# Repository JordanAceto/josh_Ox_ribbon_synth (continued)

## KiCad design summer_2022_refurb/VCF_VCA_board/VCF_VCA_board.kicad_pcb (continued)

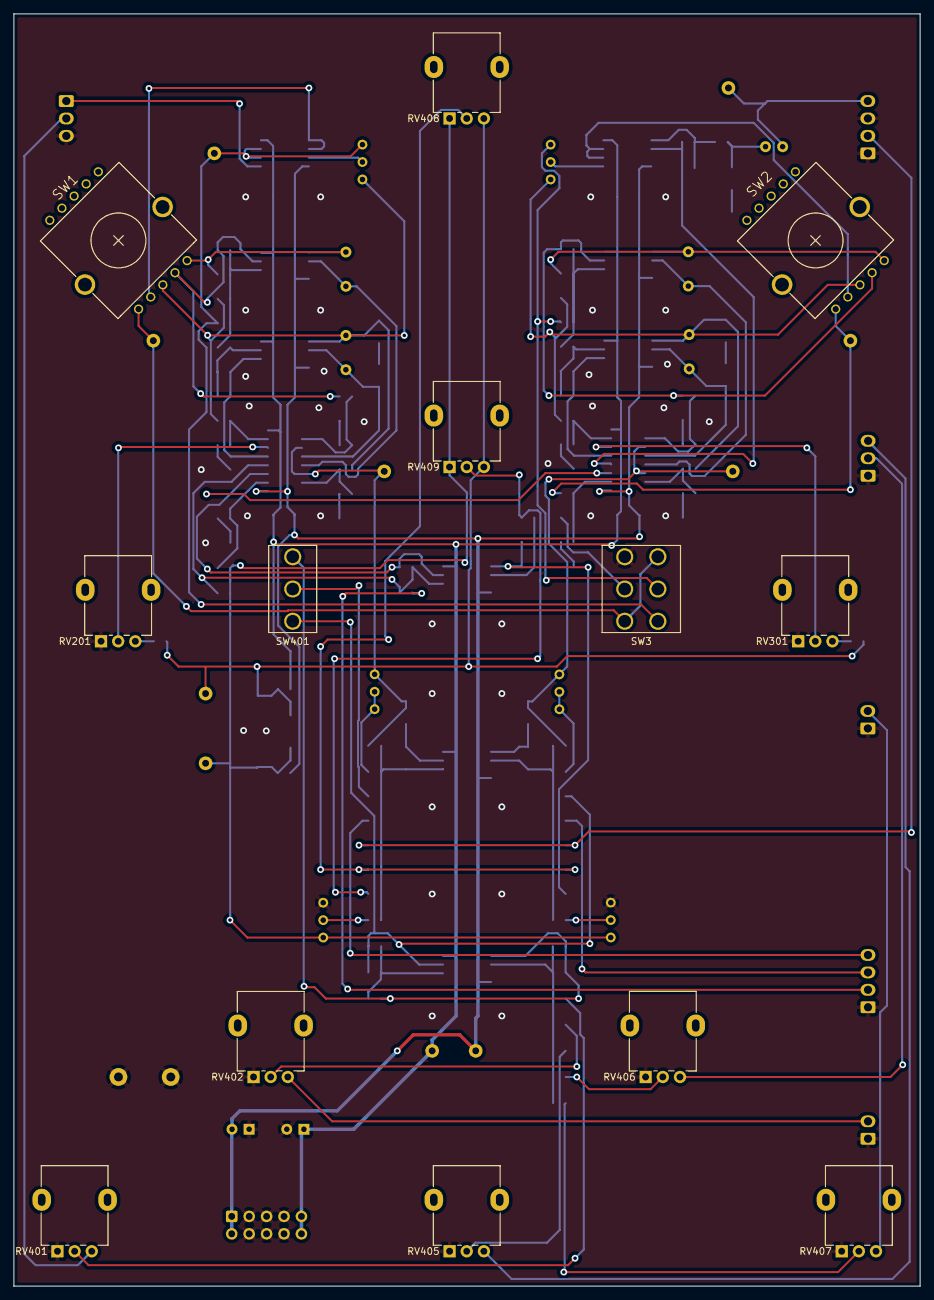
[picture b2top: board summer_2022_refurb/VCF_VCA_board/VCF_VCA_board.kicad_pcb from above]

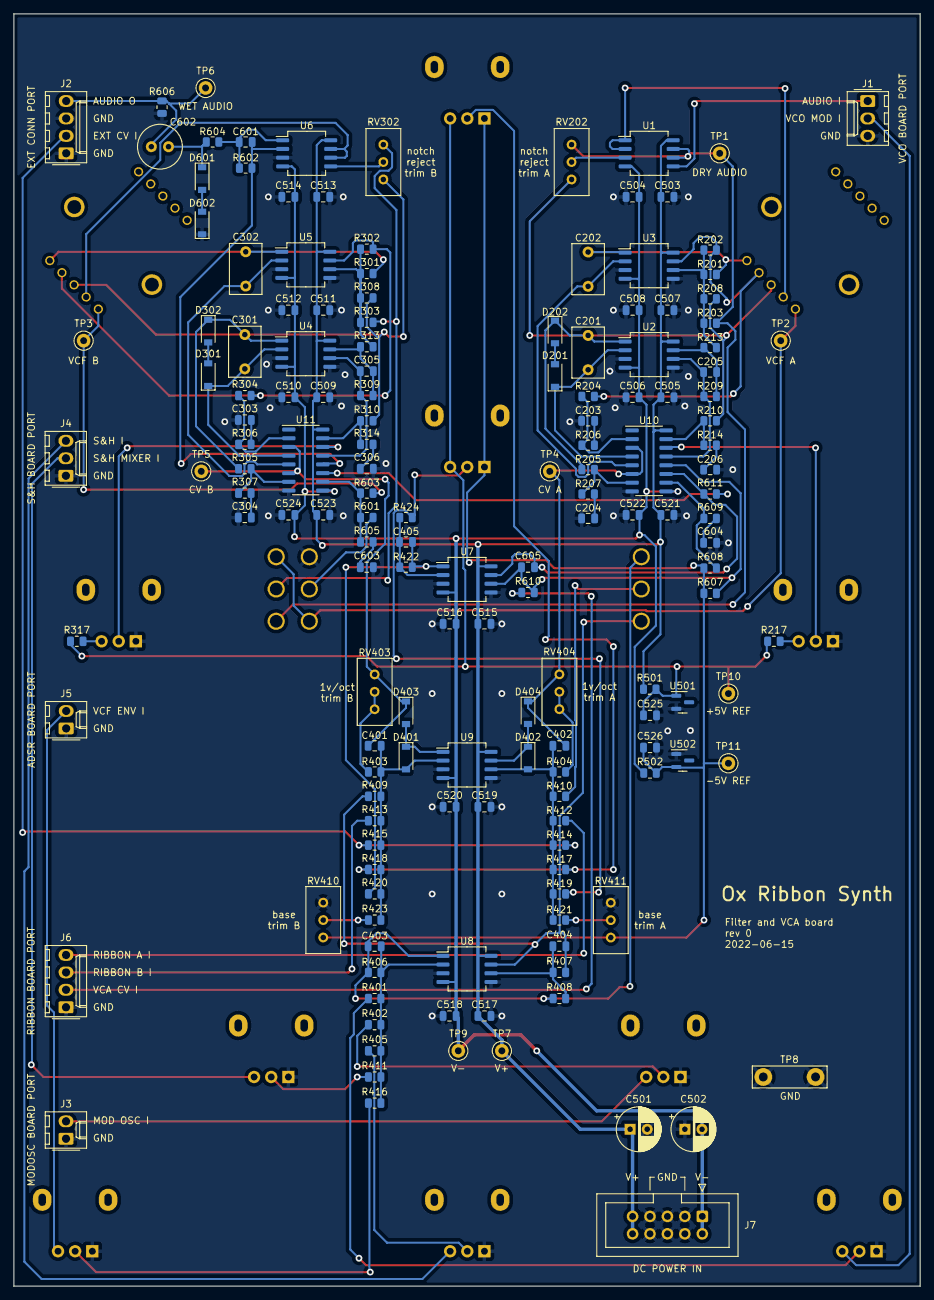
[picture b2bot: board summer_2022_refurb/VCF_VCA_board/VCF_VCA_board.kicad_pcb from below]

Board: 2 copper layers, 132.1 x 185.4 mm, 171 parts (158 on the bottom side), 94 nets.

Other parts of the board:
C301, C302: 220p; C_Rect_L7.2mm_W4.5mm_P5.00mm_FKS2_FKP2_MKS2_MKP2
C303, C304, C306: 560p; C_0805_2012Metric
C305: C; C_0805_2012Metric
D301, D302: 3v9; D_SOD-123
R301, R302, R303, R304, R305, R309, R313: 30k; R_0805_2012Metric
R306, R307, R314: 510; R_0805_2012Metric
R308: 270k; R_0805_2012Metric
R310: 15k; R_0805_2012Metric
R317: R; R_0805_2012Metric
RV301: 100k; Potentiometer_Alpha_RD901F-40-00D_Single_Vertical
RV302: 50k; Potentiometer_Bourns_3296W_Vertical

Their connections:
+5V REF: R317.1; also elsewhere on the board
/SVF_B/BP_OUT: C301.2, D302.1 (K), R305.1, R308.2, R310.2, RV302.3; also elsewhere on the board
/SVF_B/HP_OUT: R302.2, R304.1; also elsewhere on the board
/SVF_B/LP_OUT: C302.2, R301.2; also elsewhere on the board
/SVF_B/SIGNAL_IN: R303.1, RV302.1; also elsewhere on the board
unnamed 35: C301.1, D301.1 (K); also elsewhere on the board
unnamed 36: C302.1; also elsewhere on the board
unnamed: C303.1, R306.2
unnamed: C304.1, R307.2
unnamed 39: C305.1, R309.2, R313.2; also elsewhere on the board
unnamed 40: C305.2, R309.1; also elsewhere on the board
unnamed: C306.1, R314.2
unnamed: D301.2 (A), D302.2 (A)
unnamed 68: R301.1, R302.1, R303.2, R308.1, R313.1; also elsewhere on the board
unnamed 69: R304.2, R306.1; also elsewhere on the board
unnamed 70: R305.2, R307.1; also elsewhere on the board
unnamed 71: R310.1, R314.1; also elsewhere on the board
unnamed: R317.2, RV301.3
unnamed 90: RV301.2; also elsewhere on the board
unnamed 91: RV302.2; also elsewhere on the board

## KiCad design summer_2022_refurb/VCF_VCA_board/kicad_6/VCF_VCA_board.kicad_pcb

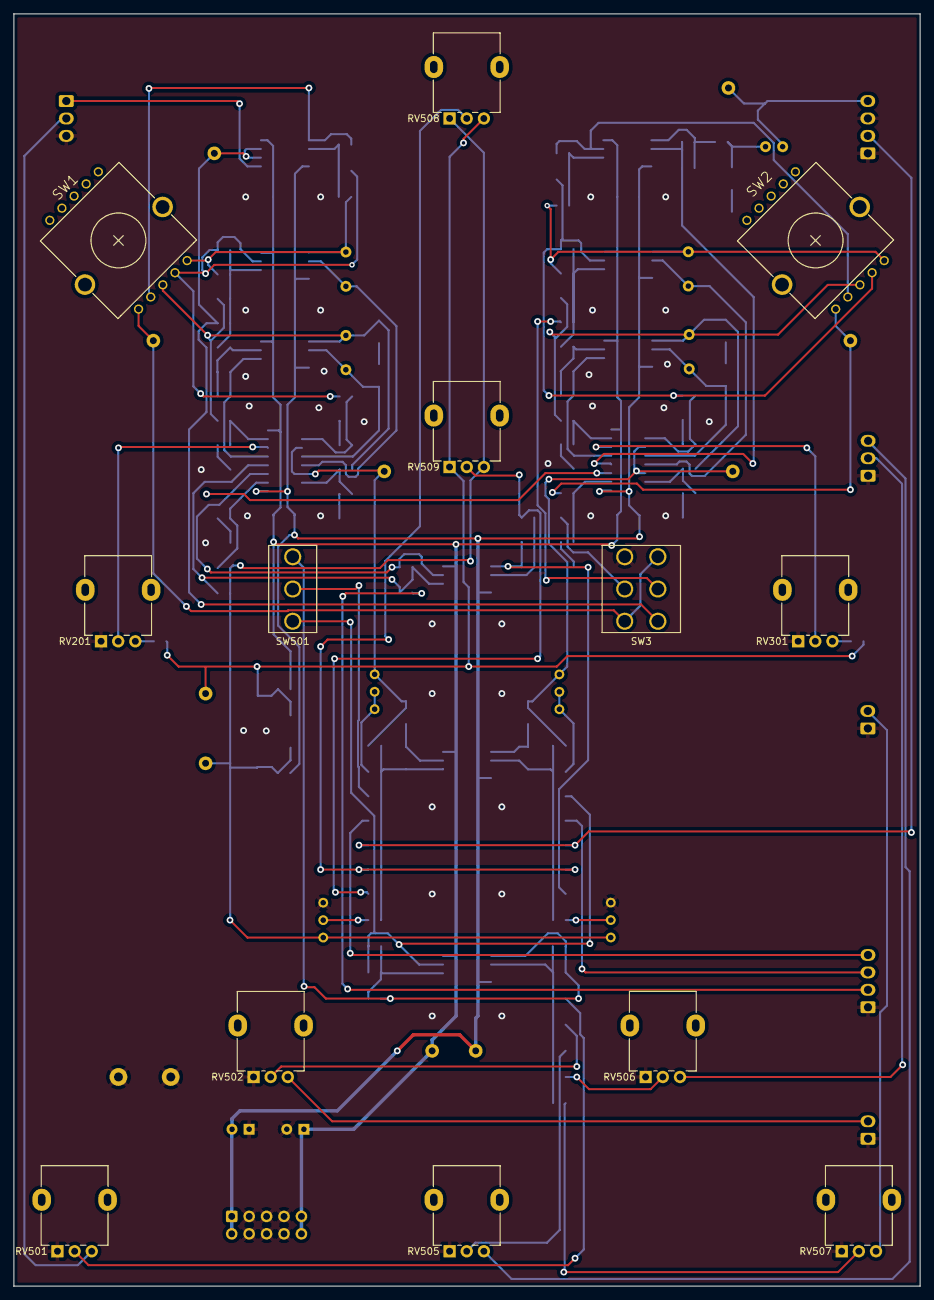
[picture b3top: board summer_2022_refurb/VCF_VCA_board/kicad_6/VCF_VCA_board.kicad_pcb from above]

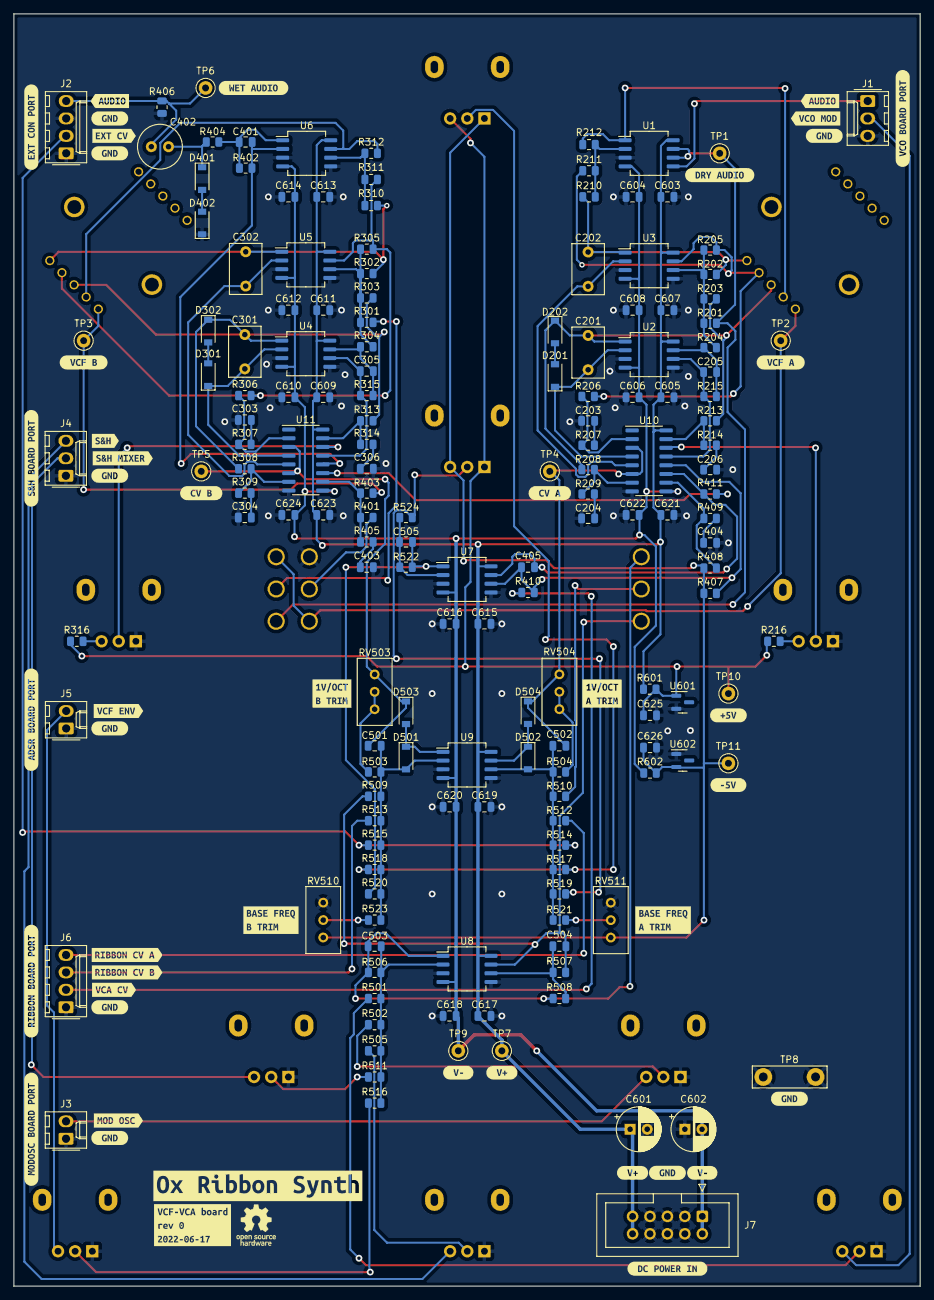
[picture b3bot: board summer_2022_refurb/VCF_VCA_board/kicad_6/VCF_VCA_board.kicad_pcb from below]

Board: 2 copper layers, 132.1 x 185.4 mm, 220 parts (207 on the bottom side), 94 nets.

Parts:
C201, C202, C301, C302: 220p; C_Rect_L7.2mm_W4.5mm_P5.00mm_FKS2_FKP2_MKS2_MKP2
C203, C204, C206, C303, C304, C306, C403, C404: 1n2; C_0805_2012Metric
C205, C305: C; C_0805_2012Metric
C401, C405, C501, C502, C503, C504, C505: 100p; C_0805_2012Metric
C402: 10u; C_Radial_D6.3mm_H5.0mm_P2.50mm
C601, C602: 10u; CP_Radial_D6.3mm_P2.50mm
C603, C604, C605, C606, C607, C608, C609, C610, C611, C612, C613, C614, C615, C616, C617, C618, C619, C620, C621, C622, C623, C624, C625, C626: 100n; C_0805_2012Metric
D201, D202, D301, D302: 3v9; D_SOD-123
D401, D402: D_Zener; D_SOD-123
D501, D502, D503, D504: 1N4148W; D_SOD-123
J1: VCO_port; Molex_KK-254_AE-6410-03A_1x03_P2.54mm_Vertical
J2: ext_port; Molex_KK-254_AE-6410-04A_1x04_P2.54mm_Vertical
J3: mod_osc_port; Molex_KK-254_AE-6410-02A_1x02_P2.54mm_Vertical
J4: S&H_port; Molex_KK-254_AE-6410-03A_1x03_P2.54mm_Vertical
J5: ADSR_port; Molex_KK-254_AE-6410-02A_1x02_P2.54mm_Vertical
J6: ribbon_port; Molex_KK-254_AE-6410-04A_1x04_P2.54mm_Vertical
J7: power_entry; IDC-Header_2x05_P2.54mm_Vertical
R201, R202, R204, R205, R206, R208, R210, R211, R212, R215, R301, R302, R304, R305, R306, R308, R310, R311, R312, R315, R401, R402, R403: 30k; R_0805_2012Metric
R203, R303: 270k; R_0805_2012Metric
R207, R209, R214, R307, R309, R314, R405, R409: 220; R_0805_2012Metric
R213, R313, R503, R504: 15k; R_0805_2012Metric
R216, R316: R; R_0805_2012Metric
R404: 1k; R_0805_2012Metric
R406, R408, R410, R501, R502, R505, R506, R507, R508, R509, R510, R511, R512, R513, R514, R515, R516, R517, R518, R522, R524: 100k; R_0805_2012Metric
R407: 2M2; R_0805_2012Metric
R411: 4k7; R_0805_2012Metric
R519, R520, R521, R523: ?; R_0805_2012Metric
R601, R602: 5k6; R_0805_2012Metric
RV201, RV301, RV501, RV502, RV505, RV506, RV507, RV508, RV509: 100k; Potentiometer_Alpha_RD901F-40-00D_Single_Vertical
RV503, RV504, RV510, RV511: 5k; Potentiometer_Bourns_3296W_Vertical
SW1, SW2: SR1712F-0204; SR1712F_rotary_switch
SW3: series_parallel_switch; DPDT_mini_toggle
SW501: SW_SPDT_center_off; SPDT_mini_toggle
TP1: DRY; TestPoint_Keystone_5000-5004_Miniature
TP2: VCF_A; TestPoint_Keystone_5000-5004_Miniature
TP3: VCF_B; TestPoint_Keystone_5000-5004_Miniature
TP4: CV_A; TestPoint_Keystone_5000-5004_Miniature
TP5: CV_B; TestPoint_Keystone_5000-5004_Miniature
TP6: FINAL_AUDIO; TestPoint_Keystone_5000-5004_Miniature
TP7: V+; TestPoint_Keystone_5000-5004_Miniature
TP8: GND; TestPoint_Bridge_Pitch7.62mm_Drill1.3mm
TP9: V-; TestPoint_Keystone_5000-5004_Miniature
TP10: REF+; TestPoint_Keystone_5000-5004_Miniature
TP11: REF-; TestPoint_Keystone_5000-5004_Miniature
U1, U2, U3, U4, U5, U6, U7, U8, U9: TL072; SO-8_5.3x6.2mm_P1.27mm
U10, U11: SSI2164; SOIC-16_3.9x9.9mm_P1.27mm
U601, U602: LM4040DBZ-5; SOT-23
kibuzzard-62AC7A9F: G***; kibuzzard-62AC7A9F
kibuzzard-62AC8A1C: G***; kibuzzard-62AC8A1C
kibuzzard-62AC8A2D: G***; kibuzzard-62AC8A2D
kibuzzard-62AC8A4C: G***; kibuzzard-62AC8A4C
kibuzzard-62AC8A9A: G***; kibuzzard-62AC8A9A
kibuzzard-62AC8A40: G***; kibuzzard-62AC8A40
kibuzzard-62AC8A61: G***; kibuzzard-62AC8A61
kibuzzard-62AC8A72: G***; kibuzzard-62AC8A72
kibuzzard-62AC8A87: G***; kibuzzard-62AC8A87
kibuzzard-62AC8B01: G***; kibuzzard-62AC8B01
kibuzzard-62AC8B2D: G***; kibuzzard-62AC8B2D
kibuzzard-62AC8B15: G***; kibuzzard-62AC8B15
kibuzzard-62AC8B47: G***; kibuzzard-62AC8B47
kibuzzard-62AC78CB: G***; kibuzzard-62AC78CB
kibuzzard-62AC88AD: G***; kibuzzard-62AC88AD
kibuzzard-62AC88C6: G***; kibuzzard-62AC88C6
kibuzzard-62AC88DA: G***; kibuzzard-62AC88DA
kibuzzard-62AC88EB: G***; kibuzzard-62AC88EB
kibuzzard-62AC89A8: G***; kibuzzard-62AC89A8
kibuzzard-62AC89C0: G***; kibuzzard-62AC89C0
kibuzzard-62AC89D1: G***; kibuzzard-62AC89D1
kibuzzard-62AC89EA: G***; kibuzzard-62AC89EA
kibuzzard-62AC755C, kibuzzard-62AC755C#2, kibuzzard-62AC755C#3, kibuzzard-62AC755C#4, kibuzzard-62AC755C#5, kibuzzard-62AC755C#6, kibuzzard-62AC755C#7, kibuzzard-62AC755C#8, kibuzzard-62AC755C#9: G***; kibuzzard-62AC755C
kibuzzard-62AC791A, kibuzzard-62AC791A#2: G***; kibuzzard-62AC791A
kibuzzard-62AC792A, kibuzzard-62AC792A#2: G***; kibuzzard-62AC792A
kibuzzard-62AC886F: G***; kibuzzard-62AC886F
kibuzzard-62AC887D: G***; kibuzzard-62AC887D
kibuzzard-62AC892A, kibuzzard-62AC892A#2: G***; kibuzzard-62AC892A
kibuzzard-62AC8760: G***; kibuzzard-62AC8760
kibuzzard-62AC8892: G***; kibuzzard-62AC8892
kibuzzard-62AC8908: G***; kibuzzard-62AC8908
kibuzzard-62AC8951: G***; kibuzzard-62AC8951
kibuzzard-62AC8974: G***; kibuzzard-62AC8974
kibuzzard-62AC8994: G***; kibuzzard-62AC8994

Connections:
+5V REF: C625.1, R216.1, R316.1, R601.2, RV508.3, RV509.1, TP10.1, U601.1 (K)
+15V: C601.1, C603.1, C605.1, C607.1, C609.1, C611.1, C613.1, C615.1, C617.1, C619.1, C621.1, C623.1, J7.9, J7.10, R601.1, TP7.1, U1.8 (V+), U2.8 (V+), U3.8 (V+), U4.8 (V+), U5.8 (V+), U6.8 (V+), U7.8 (V+), U8.8 (V+), U9.8 (V+), U10.16 (V+), U11.16 (V+)
-5V REF: C626.1, R407.1, R408.1, R602.2, RV508.1, RV509.3, RV510.3, RV511.3, TP11.1, U602.2 (A)
-15V: C602.2, C604.2, C606.2, C608.2, C610.2, C612.2, C614.2, C616.2, C618.2, C620.2, C622.2, C624.2, J7.1, J7.2, R602.1, TP9.1, U1.4 (V-), U2.4 (V-), U3.4 (V-), U4.4 (V-), U5.4 (V-), U6.4 (V-), U7.4 (V-), U8.4 (V-), U9.4 (V-), U10.9 (V-), U11.9 (V-)
/CV_mixer/MAIN_VCO: J1.2, RV501.3
/CV_mixer/MOD_OSC: J3.2, RV502.3
/CV_mixer/RIBBON_CV_A: J6.4, R512.1
/CV_mixer/RIBBON_CV_B: J6.3, R513.1
/CV_mixer/S_AND_H: J4.3, RV505.3
/CV_mixer/S_AND_H_MIXER: J4.2, RV506.3
/CV_mixer/VCF_ENV: J5.2, RV507.3
/EXT_CV: J2.2, R514.1, R515.1
/FREQ_CV_A: C502.2, D504.1 (K), RV504.1, TP4.1, U10.3, U10.6
/FREQ_CV_B: C501.2, D503.1 (K), RV503.1, TP5.1, U11.3, U11.6
/SVF_A/BP_OUT: C201.2, D202.1 (K), R203.2, R208.1, R213.2, SW1.8, U2.1
/SVF_A/HP_OUT: R205.2, R206.1, R211.1, SW1.7, U3.7
/SVF_A/LP_OUT: C202.2, R202.2, R210.1, SW1.6, U3.1
/SVF_A/NOTCH_OUT: R212.2, SW1.9, U1.1
/SVF_A/SIGNAL_IN: R201.1, SW3.4 (A), TP1.1, U1.6 (-), U1.7
/SVF_B/BP_OUT: C301.2, D302.1 (K), R303.2, R308.1, R313.2, SW2.8, U4.1
/SVF_B/HP_OUT: R305.2, R306.1, R311.1, SW2.7, U5.7
/SVF_B/LP_OUT: C302.2, R302.2, R310.1, SW2.6, U5.1
/SVF_B/NOTCH_OUT: R312.2, SW2.9, U6.7
/SVF_B/SIGNAL_IN: R301.1, SW3.5 (B)
/VCA/OUT: C402.2, J2.4, R406.1, TP6.1
/VCA/SIGNAL_IN_1: R401.1, SW3.2 (B)
/VCA/SIGNAL_IN_2: R403.1, SW2.10, TP3.1
/VCA_CV: J6.2, R410.1
GND: C203.2, C204.2, C206.2, C303.2, C304.2, C306.2, C403.2, C404.2, C601.2, C602.1, C603.2, C604.1, C605.2, C606.1, C607.2, C608.1, C609.2, C610.1, C611.2, C612.1, C613.2, C614.1, C615.2, C616.1, C617.2, C618.1, C619.2, C620.1, C621.2, C622.1, C623.2, C624.1, C625.2, C626.2, D402.1 (K), J1.3, J2.1, J2.3, J3.1, J4.1, J5.1, J6.1, J7.3, J7.4, J7.5, J7.6, J7.7, J7.8, R406.2, RV201.1, RV301.1, RV501.1, RV502.1, RV505.1, RV506.1, RV507.1, RV510.1, RV511.1, SW3.3 (C), TP8.1, U1.3 (+), U2.3 (+), U2.5 (+), U3.3 (+), U3.5 (+), U4.3 (+), U4.5 (+), U5.3 (+), U5.5 (+), U6.3 (+), U6.5 (+), U7.3 (+), U7.5 (+), U8.3 (+), U8.5 (+), U9.3 (+), U9.5 (+), U10.8 (gnd), U11.8 (gnd), U601.2 (A), U602.1 (K)
unnamed: C201.1, D201.1 (K), U2.2 (-), U10.4
unnamed: C202.1, U3.2 (-), U10.5
unnamed: C203.1, R207.2
unnamed: C204.1, R209.2
unnamed: C205.1, R204.2, R215.2, U2.7
unnamed: C205.2, R215.1, U2.6 (-), U10.13
unnamed: C206.1, R214.2
unnamed: C301.1, D301.1 (K), U4.2 (-), U11.4
unnamed: C302.1, U5.2 (-), U11.5
unnamed: C303.1, R307.2
unnamed: C304.1, R309.2
unnamed: C305.1, R304.2, R315.2, U4.7
unnamed: C305.2, R315.1, U4.6 (-), U11.13
unnamed: C306.1, R314.2
unnamed: C401.1, R402.1, U6.2 (-), U11.12
unnamed: C401.2, R402.2, R404.1, U6.1
unnamed: C402.1, D401.1 (K), R404.2
unnamed: C403.1, R405.2
unnamed: C404.1, R409.2
unnamed: C405.1, R407.2, R410.2, U7.6 (-), U10.12
unnamed: C405.2, R411.1, U7.7, U10.11
unnamed: C501.1, D501.2 (A), R503.1, R509.2, R513.2, R515.2, R518.2, R520.2, R523.2, U9.2 (-)
unnamed: C502.1, D502.2 (A), R504.1, R510.2, R512.2, R514.2, R517.2, R519.2, R521.2, U9.6 (-)
unnamed: C503.1, R501.2, R502.2, R505.2, R506.1, R511.2, R516.2, U8.2 (-)
unnamed: C503.2, R506.2, R508.1, SW501.3 (C), U8.1
unnamed: C504.1, R507.1, R508.2, U8.6 (-)
unnamed: C504.2, R507.2, R509.1, SW501.1 (A), U8.7
unnamed: C505.1, R522.1, R524.2, U7.2 (-)
unnamed: C505.2, R520.1, R522.2, U7.1
unnamed: D201.2 (A), D202.2 (A)
unnamed: D301.2 (A), D302.2 (A)
unnamed: D401.2 (A), D402.2 (A)
unnamed: D501.1 (K), D503.2 (A), U9.1
unnamed: D502.1 (K), D504.2 (A), U9.7
unnamed: J1.1, U1.5 (+)
unnamed: R201.2, R202.1, R203.1, R204.1, R205.1, U3.6 (-)
unnamed: R206.2, R207.1, U10.2
unnamed: R208.2, R209.1, U10.7
unnamed: R210.2, R211.2, R212.1, U1.2 (-)
unnamed: R213.1, R214.1, U10.15
unnamed: R216.2, RV201.3
unnamed: R301.2, R302.1, R303.1, R304.1, R305.1, U5.6 (-)
unnamed: R306.2, R307.1, U11.2
unnamed: R308.2, R309.1, U11.7
unnamed: R310.2, R311.2, R312.1, U6.6 (-)
unnamed: R313.1, R314.1, U11.15
unnamed: R316.2, RV301.3
unnamed: R401.2, R403.2, R405.1, U11.10
unnamed: R408.2, R409.1, U10.10
unnamed: R411.2, U11.11
unnamed: R501.1, RV501.2
unnamed: R502.1, RV502.2
unnamed: R503.2, RV503.2, RV503.3
unnamed: R504.2, RV504.2, RV504.3
unnamed: R505.1, RV505.2
unnamed: R510.1, SW501.2 (B)
unnamed: R511.1, RV506.2
unnamed: R516.1, RV507.2
unnamed: R517.1, R518.1, RV508.2
unnamed: R519.1, R524.1, RV509.2
unnamed: R521.1, RV511.2
unnamed: R523.1, RV510.2
unnamed: RV201.2, U10.14
unnamed: RV301.2, U11.14
unnamed: SW1.10, SW3.1 (A), SW3.6 (C), TP2.1
